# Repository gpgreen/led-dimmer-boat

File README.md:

# LED Dimmer for Boat

KiCad design for a LED strip dimmer. Provides power and switch on/off
for the board. The dimmer controls are on-off-on switch and a
rheostat. If the switch is thrown one way, we get a dimmable white
light, and if thrown the other way, we get a dimmable red light from
the LED strip.

## Functions

1. Onboard ATtiny13A
2. Power is expected to be pigtailed and soldered to board

## Firmware

The firmware project:
 - 

PCB

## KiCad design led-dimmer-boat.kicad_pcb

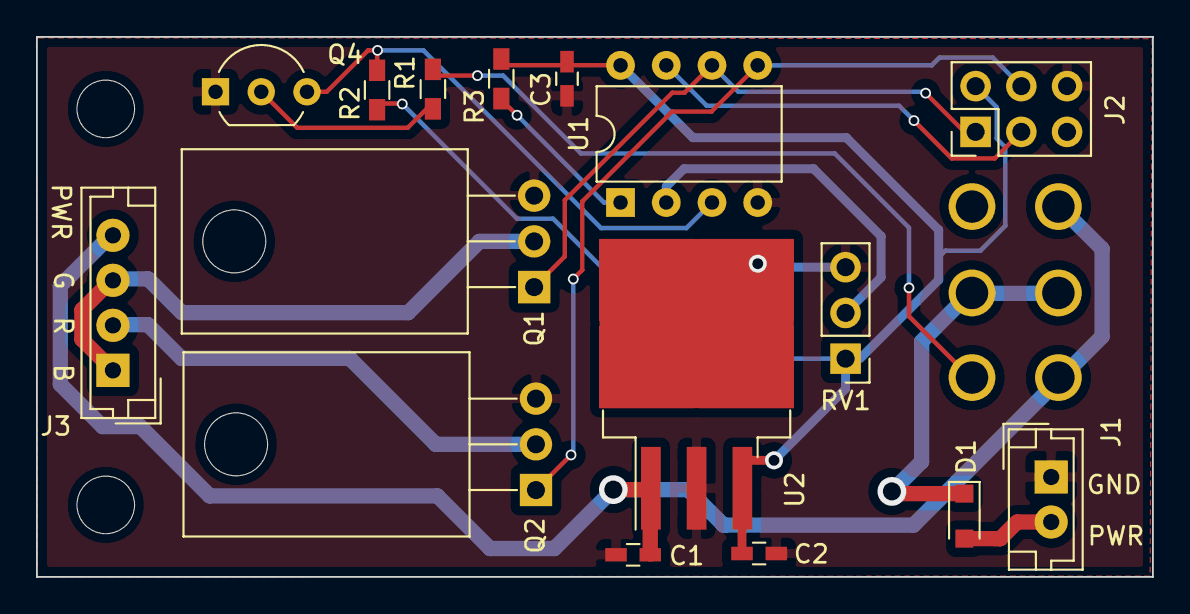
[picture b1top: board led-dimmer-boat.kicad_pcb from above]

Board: 2 copper layers, 62.0 x 30.0 mm, 19 parts (1 on the bottom side), 15 nets.

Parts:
C1: 0.22uF; C_0603_HandSoldering
C2, C3: 0.1uF; C_0603_HandSoldering
D1: 1N5400; D_SOD-323_HandSoldering
H1, H2: MountingHole; MountingHole_3.2mm_M3
J1: PWR; JST_EH_B02B-EH-A_02x2.50mm_Straight
J2: Prog; Pin_Header_Straight_2x03_Pitch2.54mm
J3: LEDSTRIP; JST_EH_B04B-EH-A_04x2.50mm_Straight
Q1, Q2: IRLB8721PBF; TO-220-3_Horizontal
Q4: 2N3904; TO-92_Inline_Wide
R1: 82K; R_0603_HandSoldering
R2: 300K; R_0603_HandSoldering
R3: 10K; R_0603_HandSoldering
RV1: R_POT; Pin_Header_Straight_1x03_Pitch2.54mm
SW1: M2023SS1W03; SW_DPDT_NKK_PC_MOUNT
U1: ATtiny13A-PU-ND; DIP-8_W7.62mm
U2: LM7805S/NOPB; TO-263-3_TabPin2

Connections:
+5V: C2.1, C3.1, J2.2, R2.1, R3.1, RV1.1, U1.8, U2.3
+12V: D1.1, SW1.2, SW1.5
B: J3.1, J3.3, Q1.2
BG_DRIVE: J2.1, Q1.1, U1.6
GND: C1.2, C2.2, C3.2, J1.1, J2.6, Q1.3, Q2.3, Q4.1, RV1.3, U1.4, U2.2
MOSI: J2.4, Q2.1, U1.5
unnamed: D1.2, J1.2
unnamed: Q4.2, R1.1
unnamed: R3.2, U1.1
POT: RV1.2, U1.2
R: J3.2, Q2.2
RED_DET: Q4.3, R2.2, U1.3
RED_SEL: R1.2, SW1.3
SCK: J2.3, U1.7
VDD: C1.1, J3.4, SW1.4, SW1.6, U2.1

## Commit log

2022-05-18 Original commit
2022-05-18 Updated schematic.pdf and added board.png
2022-05-21 Final changes for first version
2022-05-25 Added JST-EH connectors
